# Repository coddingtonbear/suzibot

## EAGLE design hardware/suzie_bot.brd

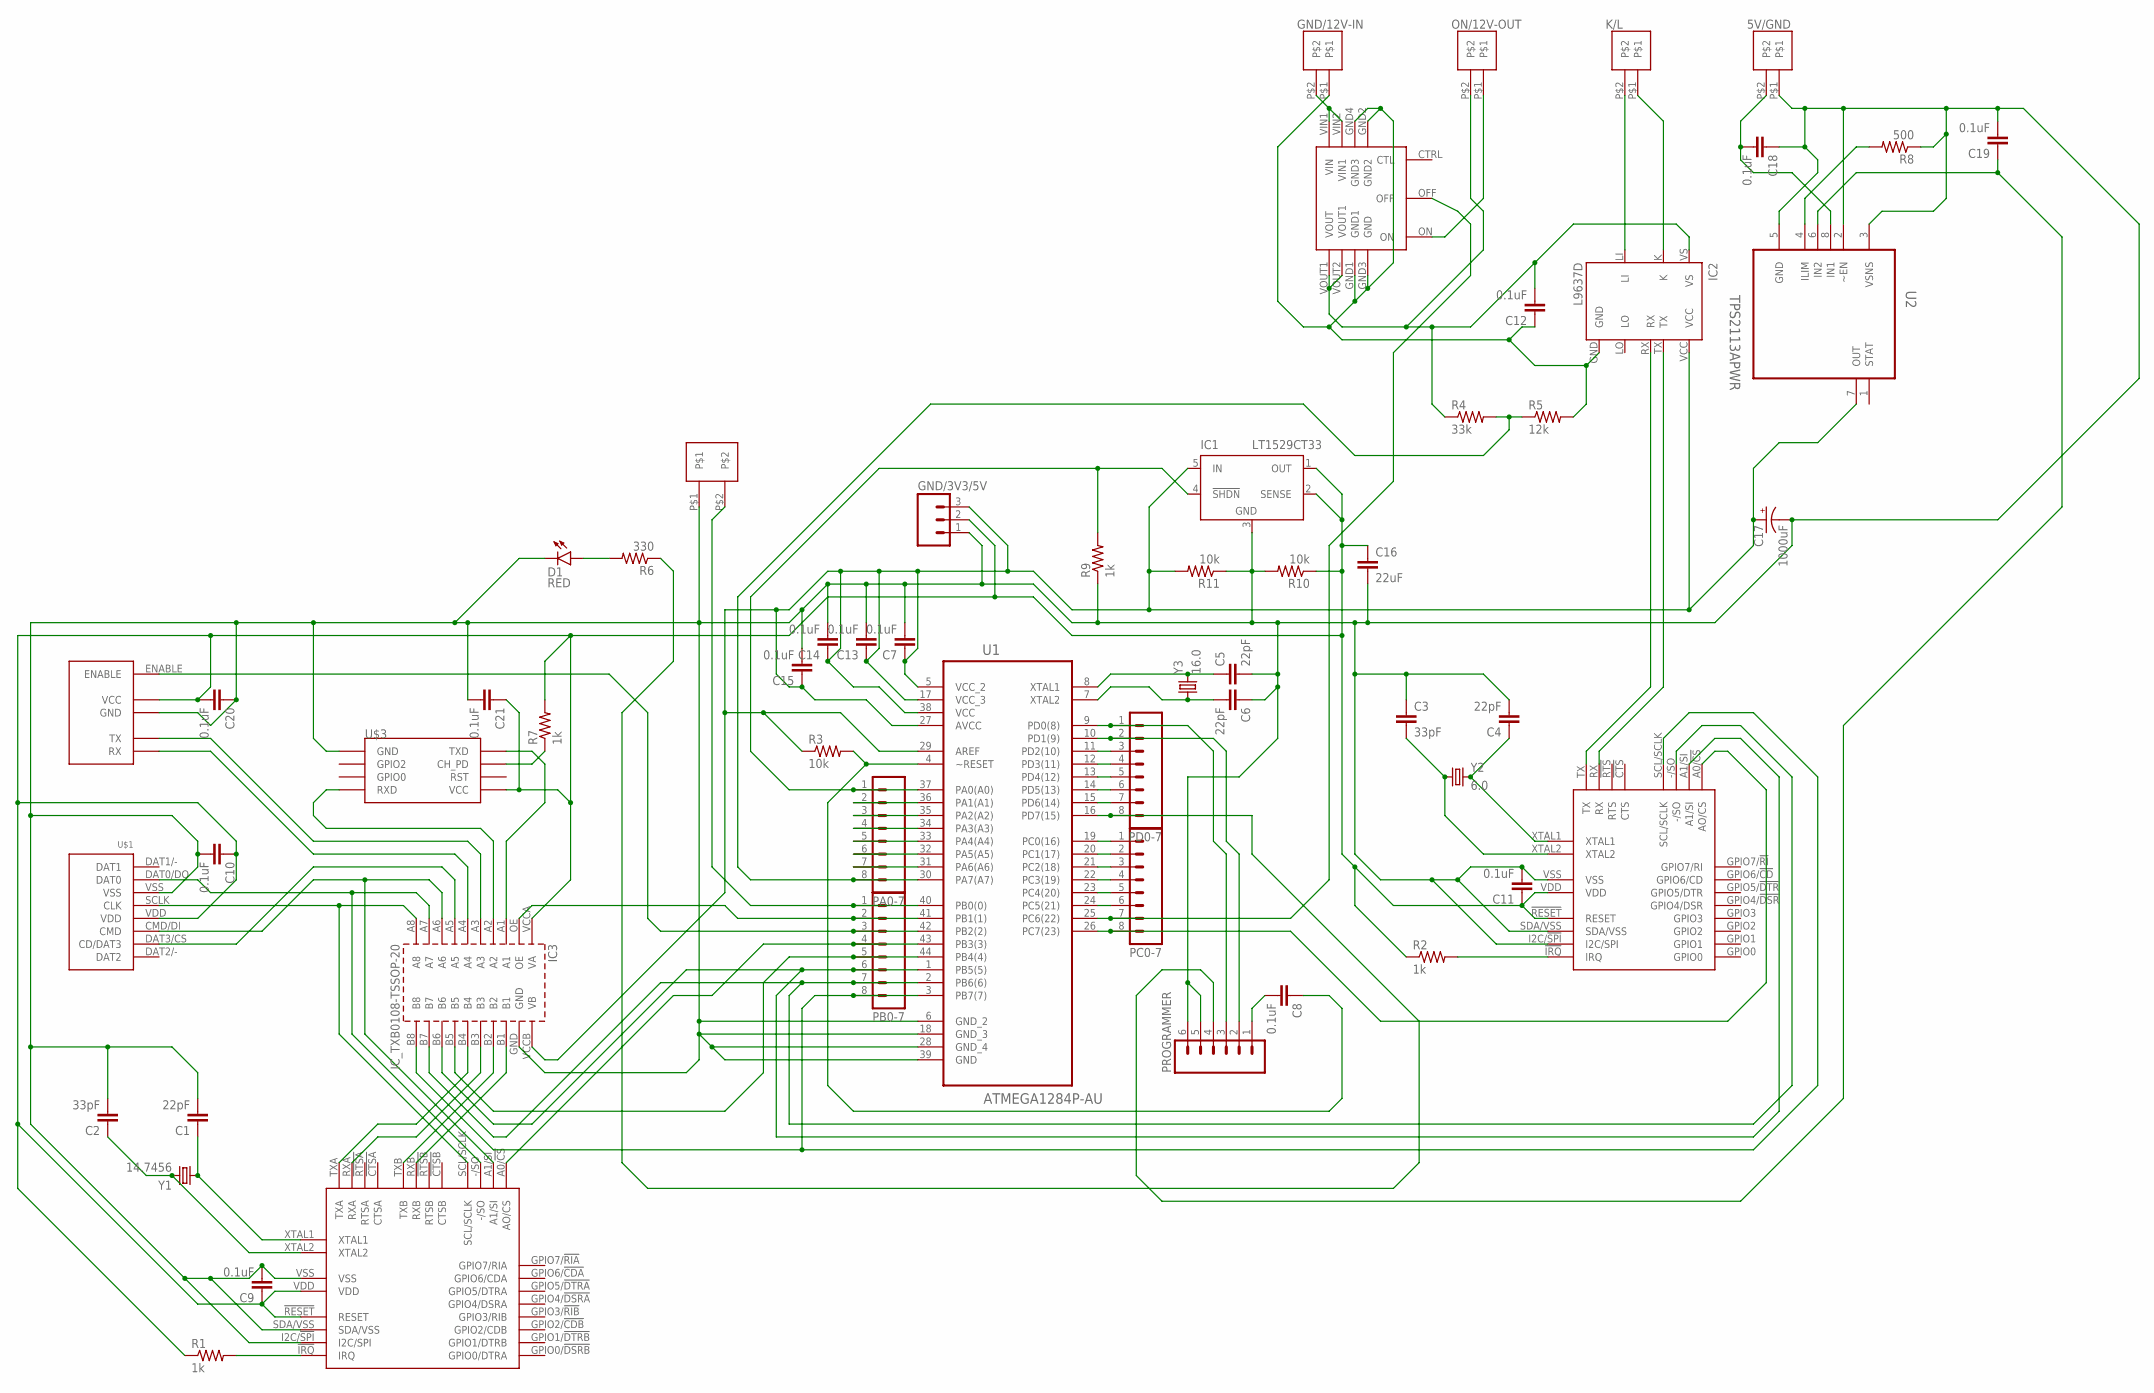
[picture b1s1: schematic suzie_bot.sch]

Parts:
5V/GND: 2-PIN-TERMINAL
C1, C4, C5, C6: 22pF; 0805
C2, C3: 33pF; 0805
C7, C9, C10, C11, C12, C13, C14, C15, C18, C19, C20, C21: 0.1uF; 0603-CAP
C8: 0.1uF; 0805
C16: 22uF; 1206
C17: 1000uF; PANASONIC_G
D1: RED; LED5MM
GND/3V3/5V: M03PTH; 1X03
GND/12V-IN: 2-PIN-TERMINAL
IC1: LT1529CT33; TO220-5
IC2: L9637D; SO08
IC3: IC_TXB0108-TSSOP-20; TSSOP-20
K/L: 2-PIN-TERMINAL
ON/12V-OUT: 2-PIN-TERMINAL
PA0-7: M08; 1X08_ROUND
PB0-7: M08; 1X08_ROUND
PC0-7: M08; 1X08_ROUND
PD0-7: M08; 1X08_ROUND
PROGRAMMER: M06SILK_FEMALE_PTH; 1X06
R1, R2, R7, R9: 1k; 0805
R3, R10, R11: 10k; 0805
R4: 33k; 0805
R5: 12k; 0805
R6: 330; 0805
R8: 500; 0805
U1: ATMEGA1284P-AU; QFP80P1200X1200X120-44N
U2: TPS2113APWR; SOP65P640X120-8N
U$1: CON_MICROSDHINGED; CON_MICROSD_HINGED
U$2: SC16IS752IPW; TSSOP28
U$3: ESP01
U$4: MINI
U$5: FEATHERWING
U$7: SC16IS750IPW; TSSOP-24
U$11: PIEZO; 17MM-PIEZO
Y1: 14.7456; HC49US
Y2: 6.0; HC49US
Y3: 16.0; HC49US

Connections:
3V3: C9.1, C10.1, C11.1, C16.1, C20.2, C21.1, GND/3V3/5V.2, IC1.1 (OUT), IC1.2 (SENSE), IC3.VCCA (VA), R1.1, R2.1, R7.2, R10.1, U$1.VDD, U$2.!RESET (RESET), U$2.VDD, U$3.VCC, U$5.VCC, U$7.!RESET (RESET), U$7.VDD
5V: C7.1, C13.1, C14.1, C15.1, C17.+, GND/3V3/5V.3, IC1.5 (IN), IC2.VCC, IC3.VCCB (VB), R3.1, R11.2, U1.5 (VCC_2), U1.17 (VCC_3), U1.27 (AVCC), U1.29 (AREF), U1.38 (VCC), U2.7 (OUT)
12V-OUT: C12.2, IC2.VS, ON/12V-OUT.P$2, R4.1, U$4.VOUT1 (VOUT), U$4.VOUT2 (VOUT1)
EXTGND: C12.1, GND/12V-IN.P$1, IC2.GND, R5.2, U$4.GND1, U$4.GND2, U$4.GND3 (GND), U$4.GND4 (GND3)
GND: 5V/GND.P$1, C1.2, C2.2, C3.1, C4.2, C5.2, C6.1, C7.2, C9.2, C10.2, C11.2, C13.2, C14.2, C15.2, C16.2, C17.-, C18.1, C19.2, C20.1, C21.2, D1.K (C), GND/3V3/5V.1, IC1.3 (GND), IC3.GND, PROGRAMMER.5, PROGRAMMER.6, R8.1, R9.1, R10.2, R11.1, U1.6 (GND_2), U1.18 (GND_3), U1.28 (GND_4), U1.39 (GND), U2.2 (~EN), U2.3 (VSNS), U2.5 (GND), U$1.VSS, U$2.I2C/!SPI (I2C/SPI), U$2.SDA/VSS, U$2.VSS, U$3.GND, U$5.GND, U$7.I2C/!SPI (I2C/SPI), U$7.SDA/VSS, U$7.VSS, U$11.P$1
K: IC2.K, K/L.P$1
L: IC2.LI, K/L.P$2
MISO3V3: IC3.A7, U$1.DAT0/DO (DAT0), U$2.-/SO
MOSI3V3: IC3.A6, U$1.CMD/DI (CMD), U$2.A1/SI
unnamed: C1.1, U$2.XTAL1, Y1.1
unnamed: D1.A, R6.2
unnamed: C2.1, U$2.XTAL2, Y1.2
unnamed: R7.1, U$3.CH_PD
unnamed: IC3.A1, U$3.TX (TXD)
unnamed: C6.2, U1.7 (XTAL2), Y3.1
unnamed: GND/12V-IN.P$2, U$4.VIN1 (VIN), U$4.VIN2 (VIN1)
unnamed: IC3.A2, U$3.RX (RXD)
unnamed: C5.1, U1.8 (XTAL1), Y3.2
unnamed: C8.2, PROGRAMMER.1
unnamed: IC3.B1, U$2.RXB
unnamed: IC3.B2, U$2.TXB
unnamed: C8.1, R3.2, U1.4 (~RESET)
unnamed: IC3.A4, U$5.RX-2 (RX)
unnamed: IC2.RX, U$7.TX
unnamed: R2.2, U$7.!IRQ (IRQ)
unnamed: IC3.B3, U$2.RXA
unnamed: R1.2, U$2.!IRQ (IRQ)
unnamed: IC2.TX, U$7.RX
unnamed: C4.1, U$7.XTAL1, Y2.2
unnamed: C3.2, U$7.XTAL2, Y2.1
unnamed: IC3.A3, U$5.TX-2 (TX)
unnamed: IC3.B4, U$2.TXA
unnamed: IC3.A5, U$1.DAT3/CS (CD/DAT3)
unnamed: IC3.OE, PB0-7.2, U1.41 (PB1(1))
unnamed: IC3.B5, PB0-7.5, U1.44 (PB4(4))
unnamed: PA0-7.7, U1.31 (PA6(A6))
unnamed: PA0-7.6, U1.32 (PA5(A5))
unnamed: C19.1, PROGRAMMER.4, U2.6 (IN2)
unnamed: R8.2, U2.4 (ILIM)
unnamed: 5V/GND.P$2, C18.2, U2.8 (IN1)
N$PD0/RXD0: PD0-7.1, PROGRAMMER.3, U1.9 (PD0(8))
PA0: IC1.4 (!SHDN), PA0-7.1, R9.2, U1.37 (PA0(A0))
PA1: PA0-7.2, U1.36 (PA1(A1))
PA2: PA0-7.3, U1.35 (PA2(A2))
PA3: PA0-7.4, U1.34 (PA3(A3))
PA4: PA0-7.5, U1.33 (PA4(A4))
PA7: PA0-7.8, R4.2, R5.1, U1.30 (PA7(A7))
PB0: PB0-7.1, U1.40 (PB0(0)), U$11.P$2
PB2: PB0-7.3, U1.42 (PB2(2)), U$5.ENABLE
PB3: PB0-7.4, U1.43 (PB3(3)), U$2.A0/!CS (AO/CS)
PB5/MOSI: IC3.B6, PB0-7.6, U1.1 (PB5(5)), U$7.A1/SI
PB6/MISO: IC3.B7, PB0-7.7, U1.2 (PB6(6)), U$7.-/SO
PB7/SCLK: IC3.B8, PB0-7.8, U1.3 (PB7(7)), U$7.SCL/SCLK
PC0: PC0-7.1, U1.19 (PC0(16))
PC1: PC0-7.2, U1.20 (PC1(17))
PC2: PC0-7.3, U1.21 (PC2(18))
PC3: PC0-7.4, U1.22 (PC3(19))
PC4: PC0-7.5, U1.23 (PC4(20))
PC5: PC0-7.6, U1.24 (PC5(21))
PC6: PC0-7.7, U1.25 (PC6(22)), U$4.OFF
PC7: PC0-7.8, U1.26 (PC7(23)), U$7.A0/!CS (AO/CS)
PD1/TXD0: PD0-7.2, PROGRAMMER.2, U1.10 (PD1(9))
PD2/RXD1: PD0-7.3, U1.11 (PD2(10))
PD3/TXD1: PD0-7.4, U1.12 (PD3(11))
PD4: PD0-7.5, U1.13 (PD4(12))
PD5: PD0-7.6, U1.14 (PD5(13))
PD6: PD0-7.7, U1.15 (PD6(14))
PD7: PD0-7.8, R6.1, U1.16 (PD7(15))
POWERON: ON/12V-OUT.P$1, U$4.ON
SKCK3V3: IC3.A8, U$1.SCLK (CLK), U$2.SCL/SCLK

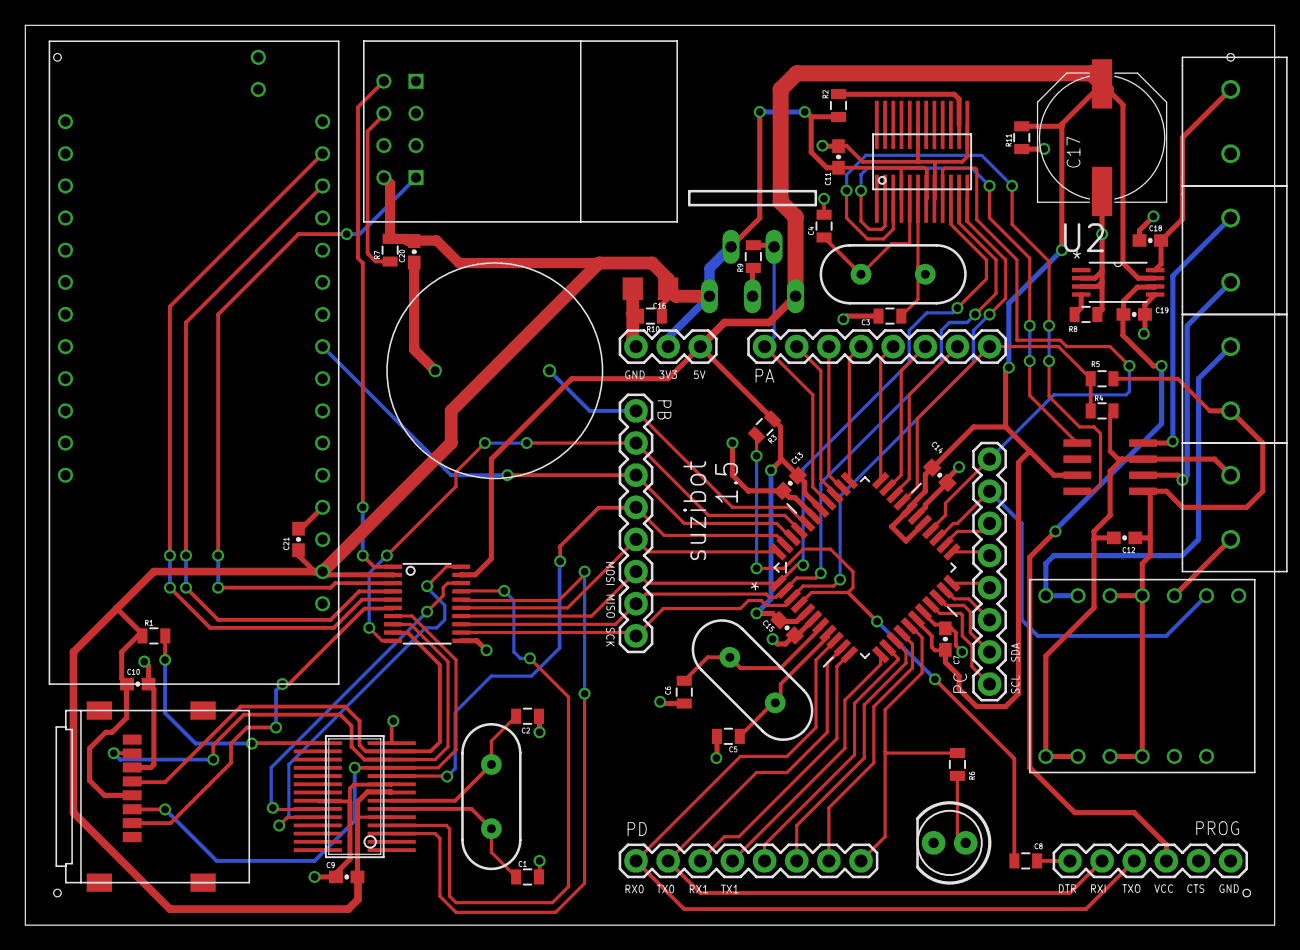
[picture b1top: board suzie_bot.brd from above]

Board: 2 copper layers, 98.7 x 71.1 mm, 58 parts (0 on the bottom side), 70 nets.

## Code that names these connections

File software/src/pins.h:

#pragma once

#define PIN_PB0 0
#define PIN_PB1 1
#define PIN_PB2 2
#define PIN_PB3 3
#define PIN_PB4 4
#define PIN_PB5 5
#define PIN_PB6 6
#define PIN_PB7 7

#define PIN_PD0 8
#define PIN_PD1 9
#define PIN_PD2 10
#define PIN_PD3 11
#define PIN_PD4 12
#define PIN_PD5 13
#define PIN_PD6 14
#define PIN_PD7 15

#define PIN_PC0 16
#define PIN_PC1 17
#define PIN_PC2 18
#define PIN_PC3 19
#define PIN_PC4 20
#define PIN_PC5 21
#define PIN_PC6 22
#define PIN_PC7 23

#define PIN_PA0 A0
#define PIN_PA1 A1
#define PIN_PA2 A2
#define PIN_PA3 A3
#define PIN_PA4 A4
#define PIN_PA5 A5
#define PIN_PA6 A6
#define PIN_PA7 A7

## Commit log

2016-09-26 And so it begins.
2016-09-26 Adding software, too.
2016-09-26 Moving software into the right folder.
2016-09-28 Latest attempts.
2016-09-29 More attempts.
2016-10-01 Another iteration.
2016-10-02 Totally working. IT WAS VOLTAGE LEVELS AND CRYSTAL CAPACITANCE PROBLEMS ALL ALONG.
2016-10-07 Basic working features.
2016-10-08 Adding a ground plane at @nbanerje's suggestion. Thanks @nbanerje!
2016-10-08 Minor changes to improve positioning.
2016-10-08 Some routing alterations; fixing SD card package sizing.
2016-10-08 Routing a bunch of wires further from the pins.
2016-10-08 Adding some text.
2016-10-09 Updating board and schematic.
2016-10-09 Updating generated PDFs.
2016-10-10 Updating board.
2016-10-10 Moving voltage sensor slightly closer to edge.
2016-10-10 Updating software.
2016-10-16 SMD-ized; pre-autorouting.
2016-10-17 Fully layed-out.
2016-10-17 Updating to include missing connection to Vout.
2016-10-17 Adding LED to PB1 (per https://www.flickr.com/photos/maniacbug/6413368937/)
2016-11-01 Updating to v1.3 boardfile (what was once an atmega328p is now an atmega1284p)
2016-11-02 Breaking out various functions into their own cpp/h files.
2016-11-04 Updating each subservice to use a class with a generic interface.
2016-11-04 Inherit from a standard class to enforce interface matching.
2016-11-07 Much better decoupling; adding TI TPS2113A for limiting inrush current.
2016-11-08 Start board with 3V3 rail disabled; enable after ~1s (long enough for caps to charge)
2016-11-08 Remove dependence upon ESP8266.
2016-11-08 Add assertion/deassertion of SPI bus for SD card interactions.
2016-11-08 Adding 1k pullup resistor for disabling 3V3 regulator until MC-enabled.
2016-11-28 Updating to include EventManager.
2016-11-30 Minor build changes; switching back to high-speed SPI.
2016-11-30 Minor changes to timing and cleanup.
2016-11-30 Updating to latest board version.
2016-11-30 Switch to pin names rather than using artificially-assigned mightycore pin numbers.
2016-11-30 Adding ArduinoJson and EventManager.
2016-12-03 Applying some new knowledge from @KateGregory's C++ introduction course.
2016-12-04 Switching from .ino format to .cpp/.h
2016-12-04 3s is enough, apparently.
2016-12-04 Converting EventManager to instead accept a String* to allow for JSON responses.
2016-12-05 Working event bus.
2016-12-05 Adding code for incrementally building buffers for wifimanager.
2016-12-05 Adding basic callback workflow for WifiManager.
2016-12-06 Move LED lighting into system manager.
2016-12-07 Adding some structure.
2016-12-21 Adding new 'suzibot-shield' subproject.
2016-12-22 New version of shield.
2016-12-22 Fully-routed; just the wrong size.
2016-12-23 Fully routed and with parts in reasonably OK spots.
2016-12-24 Fully working; switched to USB MINI B.

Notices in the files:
parts and their libraries:
SparkFun-Passives: Licensing: Creative Commons ShareAlike 4.0 International - https://creativecommons.org/licenses/by-sa/4.0
